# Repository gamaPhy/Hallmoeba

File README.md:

# Hallmoeba

This repository contains assets for the Hallmoeba, a single-switch PCB for Gateron's KS-20 Hall effect switch. It is also compatible with Wooting's Lekker switch, which is based on the KS-20.

## DIY Breadboard analog keypad made with Hallmoeba

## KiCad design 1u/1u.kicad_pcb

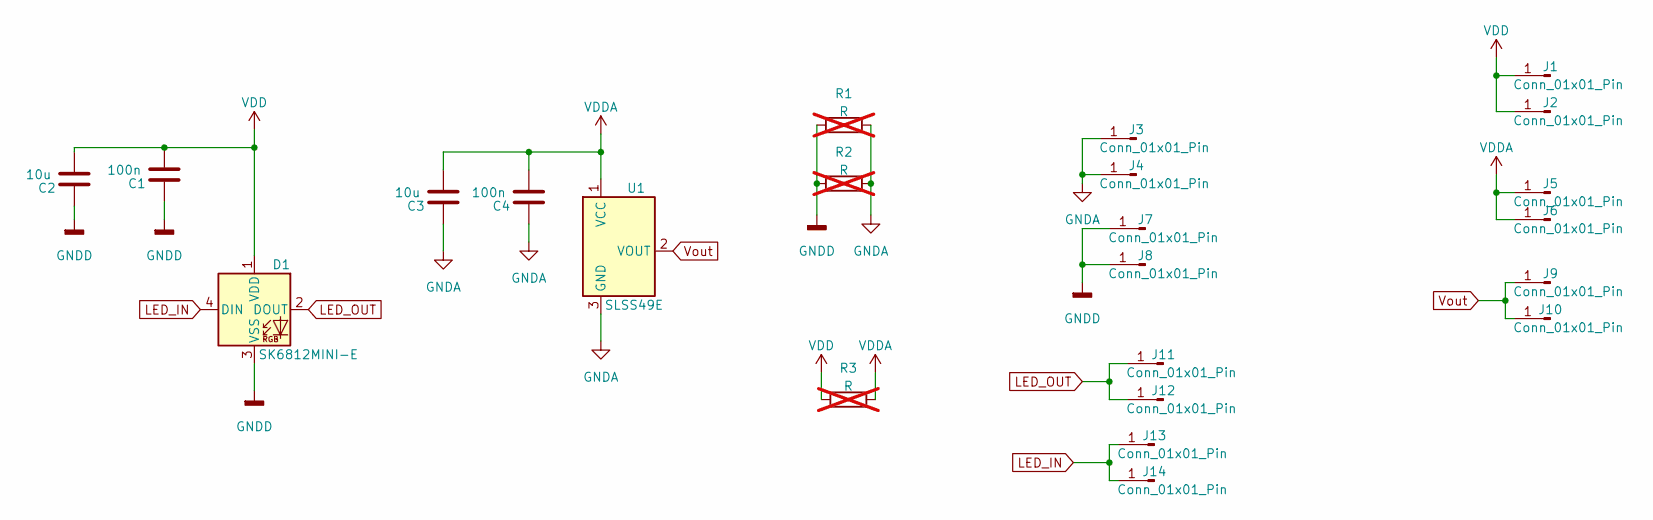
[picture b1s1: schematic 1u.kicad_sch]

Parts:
C1, C4: 100n; C_0603_1608Metric
C2, C3: 10u; C_0603_1608Metric
D1: SK6812MINI-E; SK6812MINI_E
J1, J2, J3, J4, J5, J6, J7, J8, J9, J10, J12, J14: Conn_01x01_Pin; PinHeader_1x01_P2.54mm_Vertical
J11, J13: Conn_01x01_Pin; PinHeader_1x01_P1.27mm_Vertical
R1, R2, R3: R; R_0402_1005Metric_Pad0.72x0.64mm_HandSolder; not fitted
U1: SLSS49E; SOT-23-3

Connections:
GNDA: C3.1, C4.1, J3.1, J4.1, R1.2, R2.2, U1.3 (GND)
GNDD: C1.1, C2.1, D1.3 (VSS), J7.1, J8.1, R1.1, R2.1
LED_IN: D1.4 (DIN), J13.1, J14.1
LED_OUT: D1.2 (DOUT), J11.1, J12.1
VDD: C1.2, C2.2, D1.1 (VDD), J1.1, J2.1, R3.1
VDDA: C3.2, C4.2, J5.1, J6.1, R3.2, U1.1 (VCC)
Vout: J9.1, J10.1, U1.2 (VOUT)

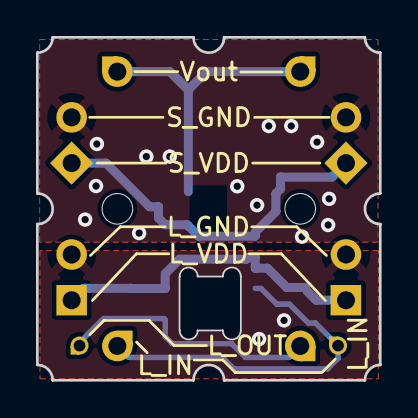
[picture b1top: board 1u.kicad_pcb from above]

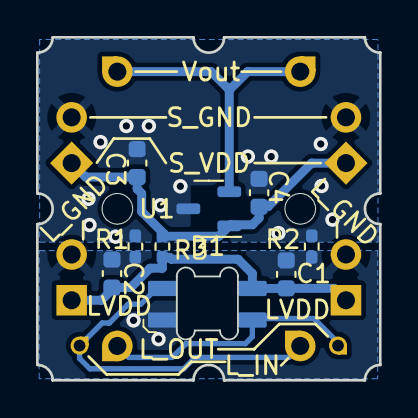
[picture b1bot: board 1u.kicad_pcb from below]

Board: 2 copper layers, 19.1 x 19.0 mm, 24 parts (23 on the bottom side), 7 nets.

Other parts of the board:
SW: SW_Lekker_MX_1.00u_PCB

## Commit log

2023-03-27 Finish PCB
2023-03-28 makes sensor matrix
2023-03-28 removes vias within hall sensor
2023-03-28 adds another row to matrix
2023-03-28 adds more test fixtures
2023-03-30 adds tb
2023-03-30 finishing touches
2023-03-30 adds vdd and vdd connection pads
2023-03-30 vdda and vdd connection
2023-03-30 moves holes and adds silkscreen
2023-03-30 move tabs
2023-03-31 moves GND shorts
2023-03-31 changes hole sizes to m1.6
2023-03-31 fix screw hole
2023-03-31 fix tabs
2023-03-31 adds panelization tabs
2023-03-31 changes tabs
2023-03-31 adds 1x3 breadboard plate
2023-04-01 shrink 1x1 and add 2u outline
2023-04-02 fixes kikit tabs
2023-04-02 adds silkscreen to 1x1
2023-04-02 fixes left and right tabs
2023-04-02 make symmetric
2023-04-02 fix edge cuts
2023-04-02 remove duplicate tabs
2023-04-03 move bottom trace up a bit
2023-04-03 add custom kikit script for tabs and to fix mousebites
2023-04-03 make the 1u taller by a tiny bit
2023-04-03 tweak stabilizer to match 1u
2023-04-03 rename stuff
2023-04-03 updates 1x3 breadboard plate for new dimensions
2023-04-04 converts to 19.05x19.05mm
2023-04-04 fixes silkscreen
2023-04-07 switch to vcuts
2023-04-07 remove 2u_stabilizer (moved to branch)
2023-04-07 cleanup
2023-04-08 Create LICENSE
2023-04-08 adds copyright notice
2023-04-08 change pcb name
2023-04-18 change silkscreen
2023-04-23 adds production files
2023-06-25 increase mounting hole size to M2. remove tabs and plate
2023-06-26 adds jlc prod files
2023-06-26 changes gitignore to add all jlc prod files
2023-08-04 Removes broken image link from README.md
2023-09-21 adds fritzing related stuff
2023-09-21 adds more fritzing info and changes files to jpg
2023-09-30 adds build guide link in readme
2023-10-24 updates fritzing wiring to match keypad pcb
2023-12-02 connects 3v3 out to ADC_VREF in fritzing diagram to match up with Freedom-3k
2024-12-14 initial build guide
2024-12-14 change name of build guide
2024-12-14 adds new assets and moves some assets from other directories here
2024-12-14 adds pictures back into build guide
2024-12-14 fix asset typo
2024-12-14 adds in correct path for remaining images
